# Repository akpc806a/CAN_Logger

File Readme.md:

# CAN Bus Logger / Playback Device with SD-card

The device can be used to log data from any CAN-bus based application: vehicle, automation, robotics, etc. The log is stored in comma separated text file (CSV) and each log entry (CAN-message) has a time stamp. It also has playback function, i.e. can play recorded file back onto a CAN bus, turning the device into a CAN bus simulator. The logger is an ideal solution for applications where small, cheap and simple device is needed to record CAN-bus activity without any additional hardware.

## Features

- The device has only one start/stop button, and all the settings are stored in configuration text file on SD card. No external PC or smartphone is required for logger operation.
- Bitrates up to 1 Mbps (any non-standard baud rate supported), supports CAN 2.0A (11-Bit ID) and CAN 2.0B (29-Bit ID).
- Optional message filtering based on ID mask matching.
- Selectable listen-only mode (without CAN bus acknowledge).
- Three LEDs for indication of logger status.
- Playback function with time accuracy of 3 ms.
- Open source and open hardware project.

## Specification

- Support for up to 32GB micro-SD cards (FAT32), for best results the UHS Speed Class 1 (U1) SD card recommended.
- Power supply voltage: from +5V to +20V DC.
- Dimensions: 48.26 x 20.85 mm (1.9 x 0.82 in).
- Microcontroller: STM32F405RGT6 (ARM Cortex M4).

## Where to buy ready made device

- [My Tindie store](https://www.tindie.com/products/akpc806a/can-bus-logger-with-sd-card/)
- [eBay](https://www.ebay.com/sch/i.html?_from=R40&_trksid=p2380057.m570.l1313.TR0.TRC0.H0.XCAN+Bus+Logger+with+SD-card.TRS5&_nkw=CAN+Bus+Logger+with+SD-card&_sacat=0)

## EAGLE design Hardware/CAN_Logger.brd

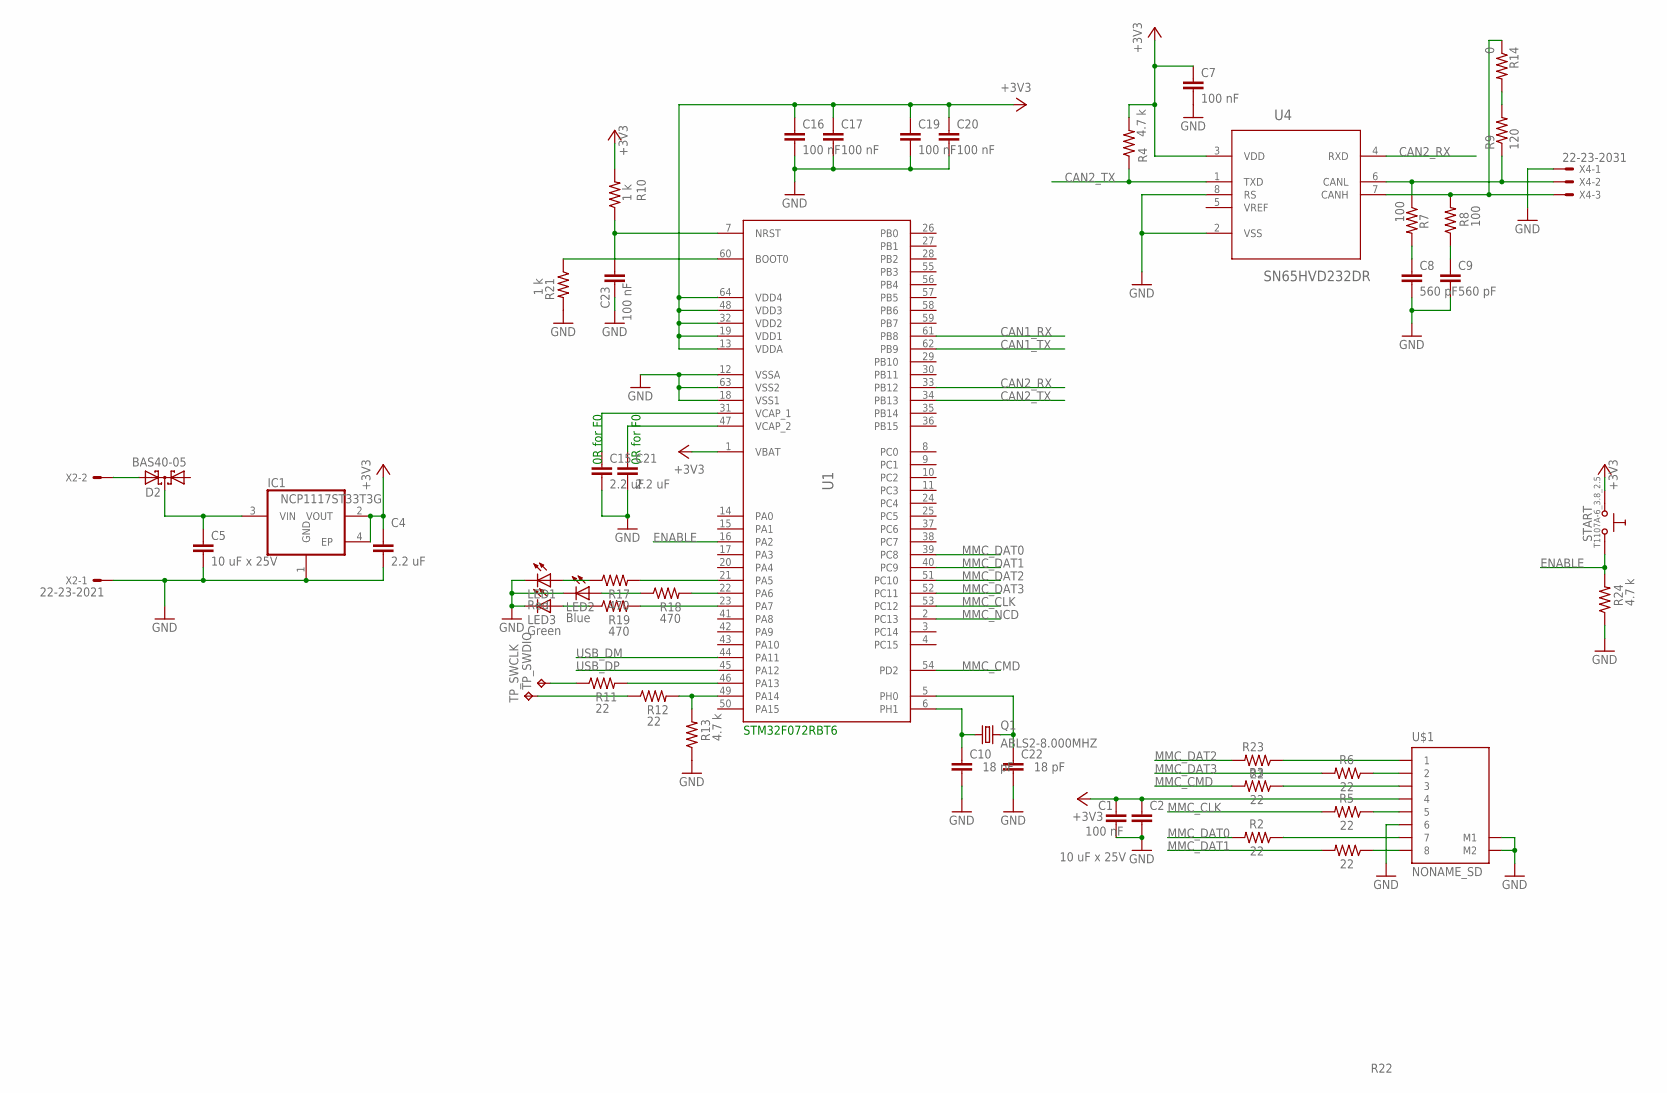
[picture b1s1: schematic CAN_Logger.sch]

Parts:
C1, C7, C16, C17, C19, C20, C23: 100 nF; C0603
C2, C5: 10 uF x 25V; C1206
C4, C15, C21: 2.2 uF; C0603
C8, C9: 560 pF; C0603
C10, C22: 18 pF; C0603
D2: BAS40-05; SOT23
IC1: NCP1117ST33T3G; SOT223
LED1: Red; LED_SML0603
LED2: Blue; LED_SML0603
LED3: Green; LED_SML0603
Q1: ABLS2-8.000MHZ; SM49
R2, R3, R5, R6, R11, R12, R22, R23: 22; R0603
R4, R13, R24: 4.7 k; R0603
R7, R8: 100; R0603
R9: 120; R0805
R10, R21: 1 k; R0603
R14: 0; R0201
R17, R18, R19: 470; R0603
START: T1107A-6_3.8_2.5; SW-TAKT_6X3.5_SMD
TP_SWCLK: TPTP10SQ; TP10SQ
TP_SWDIO: TPTP10SQ; TP10SQ
U1: STM32F405RGT6; LQFP64
U4: SN65HVD232DR; SOIC127P600X175-8N
U$1: NONAME_SD
X2: 22-23-2021
X4: 22-23-2031

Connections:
+3V3: C1.1, C2.1, C4.1, C7.1, C16.1, C17.1, C19.1, C20.1, IC1.2 (VOUT), IC1.4 (EP), R4.2, R10.2, START.P$1 (0), U1.1 (VBAT), U1.13 (VDDA), U1.19 (VDD1), U1.32 (VDD2), U1.48 (VDD3), U1.64 (VDD4), U4.3 (VDD), U$1.4
CAN1_RX: U1.61 (PB8)
CAN1_TX: U1.62 (PB9)
CAN2_RX: U1.33 (PB12), U4.4 (RXD)
CAN2_TX: R4.1, U1.34 (PB13), U4.1 (TXD)
ENABLE: R24.2, START.P$2 (1), U1.16 (PA2)
GND: C1.2, C2.2, C4.2, C5.2, C7.2, C8.2, C9.2, C10.2, C15.2, C16.2, C17.2, C19.2, C20.2, C21.2, C22.2, C23.2, IC1.1 (GND), LED1.C, LED2.C, LED3.C, R13.1, R21.2, R24.1, U1.12 (VSSA), U1.18 (VSS1), U1.63 (VSS2), U4.2 (VSS), U4.8 (RS), U$1.6, U$1.M1, U$1.M2, X2.1, X4.1
MMC_CLK: R5.2, U1.53 (PC12)
MMC_CMD: R3.2, U1.54 (PD2)
MMC_DAT0: R2.2, U1.39 (PC8)
MMC_DAT1: R22.2, U1.40 (PC9)
MMC_DAT2: R23.2, U1.51 (PC10)
MMC_DAT3: R6.2, U1.52 (PC11)
MMC_NCD: U1.2 (PC13)
unnamed: C15.1, U1.31 (VCAP_1)
unnamed: D2.2 (A2), X2.2
unnamed: R3.1, U$1.3
unnamed: R2.1, U$1.7
unnamed: R5.1, U$1.5
unnamed: R17.2, U1.21 (PA5)
unnamed: R7.1, R9.1, U4.6 (CANL), X4.2
unnamed: C5.1, D2.3 (C), IC1.3 (VIN)
unnamed: R8.2, R14.1, U4.7 (CANH), X4.3
unnamed: R6.1, U$1.2
unnamed: C8.1, R7.2
unnamed: C9.1, R8.1
unnamed: R18.2, U1.22 (PA6)
unnamed: R19.2, U1.23 (PA7)
unnamed: LED1.A, R17.1
unnamed: LED2.A, R18.1
unnamed: LED3.A, R19.1
unnamed: R22.1, U$1.8
unnamed: R23.1, U$1.1
unnamed: R11.2, U1.46 (PA13)
unnamed: R12.2, R13.2, U1.49 (PA14)
unnamed: C21.1, U1.47 (VCAP_2)
unnamed: R11.1, TP_SWDIO.TP
unnamed: R12.1, TP_SWCLK.TP
unnamed: C23.1, R10.1, U1.7 (NRST)
unnamed: R21.1, U1.60 (BOOT0)
unnamed: R9.2, R14.2
unnamed: C22.1, Q1.2, U1.5 (PH0)
unnamed: C10.1, Q1.1, U1.6 (PH1)
USB_DM: U1.44 (PA11)
USB_DP: U1.45 (PA12)

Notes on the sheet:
STM32F072RBT6
0R for F0

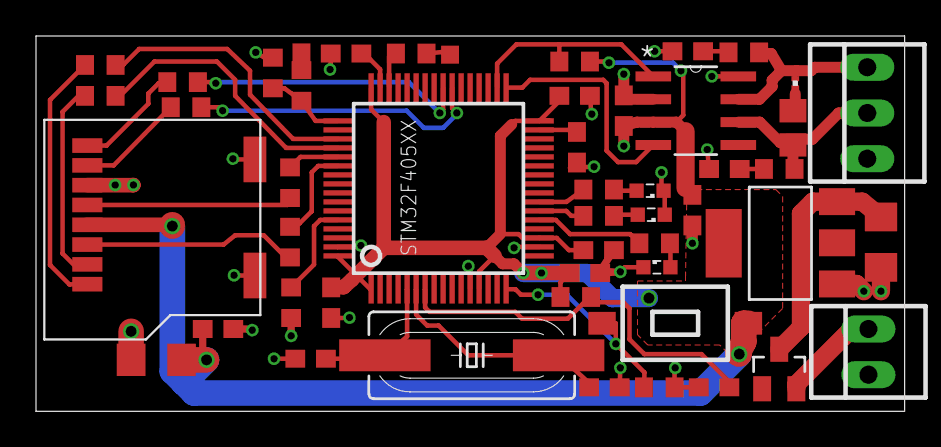
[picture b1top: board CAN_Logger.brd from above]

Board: 2 copper layers, 48.3 x 20.8 mm, 50 parts (0 on the bottom side), 40 nets.

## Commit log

2016-11-20 ChibiStudio project added
2016-11-25 baudrate bug fixed, use case test data added
2016-11-27 source code cleared, pdf and hex files added
2016-11-27 documentation added
2016-12-03 minor correction to documentation
2017-01-18 updated to hardware revision 2
2017-01-28 tiny update of doc/pdf
2017-02-16 replay the logs to CAN mode (initial)
2017-02-17 replay the log to CAN mode (tested)
2017-02-17 added documentation for playback mode
2017-02-18 hex file updated
2017-02-19 tiny correction to documentation
2017-03-18 readme file added for main page
2017-09-19 critical section added
2017-09-19 corrected link in Readme
2017-10-10 Fix CSV header
2018-01-05 extended ID fix
    also full header line
2018-07-16 additional configuartion options for start/stop logs implemented
    start_on_power, circular_write, start_id, stop_id, start_on_CAN, stop_on_CAN, start_frame_to_name
2018-07-16 long file names for file names recovered from CAN message
2018-07-23 reverted back to 8.3, gap detection in file names (under wraping)
2018-08-06 Manual is updated
